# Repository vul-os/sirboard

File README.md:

<h1 align="center">SirBoard</h1>

<p align="center">
  <b>Open hardware for people who would rather prototype than reflow.</b><br>
  107 PCB designs — breakout adapters, development boards and a 39-part sensor line.<br>
  Routed in KiCad. Black soldermask, ENIG gold, 0.1&Prime; pitch.
</p>

## Brand

The mark in [`brand/`](brand/) is the source of truth. Every icon this repo
ships — favicon, PWA and app icons, the mark in the README and on the site — is
rendered from `brand/logo.svg` rather than redrawn, so there is one approved
drawing and no second copy to drift.

Copy it outward, never edit a derived copy, and never edit `brand/` to match
something downstream.

<p align="center">
  <a href="https://vulos.org/projects/sirboard"><b>vulos.org/projects/sirboard</b></a>
  ·
  <a href="docs/OVERVIEW.md">Docs</a>
  ·
  <a href="LICENSE-MIT">MIT OR Apache-2.0</a>
</p>

<p align="center">
  
</p>

---

Most interesting silicon ships in a package that will not sit on a breadboard.
SirBoard answers that in three layers: **bare adapters** you solder the part
onto yourself, **modules** with the part already placed and supported, and
**development boards** with a microcontroller, regulator, USB and headers.

## What's here

| Directory | Contents |
|---|---|
| [`Boards/Breakout/`](Boards/Breakout) | **21 adapters** — QFN, TQFP, SOIC, SOT, USB, MicroSD, coin cells, ESP module carriers |
| [`Boards/Microcontrollers/`](Boards/Microcontrollers) | ATTiny, ATMega328PB/32U4/1284P, ESP32/ESP8266 and SIMCom GNSS carriers |
| [`Boards/Interface/`](Boards/Interface) | USB-to-UART bridges, level shifters, port expanders, a USBASP programmer |
| [`Boards/Sensors/`](Boards/Sensors) | **SirBlue** — 39 digital sensors on one 4-pin JST-SH connector, plus two earlier collections (DigitalSensors 12, AnalogueSensors 2) |
| [`Boards/Modules/`](Boards/Modules) | EEPROM, FRAM, real-time clocks — 5 designs |
| [`Fritzing/`](Fritzing) | 60 hand-drawn breadboard SVGs |

## Quick start

```bash
git clone git@github.com:vul-os/sirboard.git
cd sirboard

# most designs ship a plotted PDF and renders — no tools needed to read one
open Boards/Microcontrollers/SirTiny/ATTinyX16/ATTinyX16.pdf

# or open the project itself
kicad Boards/Microcontrollers/SirTiny/ATTinyX16/ATTinyX16.pro
```

These are **KiCad 5** files (board format `20171130`). KiCad 6 through 9 open
them and offer to convert on save.

## What state is this in?

Hardware repositories rot by ambiguity, so here it is plainly.

**Can you get these made? Yes.** Every one of the 107 designs is fully routed
2-layer copper with a board outline, and plots to gerbers from source with
`kicad-cli` or File → Plot. Nothing here needs a blind via, a buried via,
controlled impedance or a non-standard stack-up, and every outline fits inside a
100 × 100 mm panel. Seven of the fine-pitch breakouts need a 5 mil process
rather than 6 mil — they are named in
[Manufacturing](docs/MANUFACTURING.md#the-5-mil-figure-is-not-decoration--quote-it-to-the-fab).

**What is *not* claimed.** No DRC or ERC report is committed for any board, and
no fabrication or bring-up log exists in this repository. The `_Front`/`_Back`/
`_Iso` images are KiCad 3D-viewer renders, not photographs of assembled boards —
so do not read them as proof that a given design was built and worked. Treat
every design as prototype-grade: **run DRC yourself and read the schematic
before you spend money on a panel.** The catalogue has shipped at least one
unconnected trace in the past (commit `28e6714`, on the TQFP48 breakout), which
is exactly the class of defect a DRC run catches and a render does not.

**Is it maintained?** The designs are stable rather than actively developed. Two
directories under `Boards/` hold a README and no design —
[`Sensors/SirRed`](Boards/Sensors/SirRed) (an analogue line on a 3-pin JST-SH)
and [`Modules/SirReference`](Boards/Modules/SirReference) (voltage references) —
and they are stated intent, not work in progress; neither is counted in the 107.
What *is* maintained is the repository's honesty:
[CI](.github/workflows/ci.yml) gates the counts, coverage tables and fab
figures in these docs against the actual `.kicad_pcb` files on every push, so a
claim here cannot quietly drift away from the copper. Fixes to existing designs
are the most welcome kind of change.

## The sensor line

Every [SirBlue](Boards/Sensors/SirBlue) board carries the same 4-pin 1.00 mm JST-SH
connector — `GND · VCC · SDA · SCL` — and the same outline. One cable fits all
39 parts, so swapping an accelerometer for a time-of-flight ranger is a
connector move rather than a rewire. A
[TCA9548A](Boards/Interface/SirExpand/TCA9548A) multiplexer handles the address
collisions when you want eight of the same part.

## We don't ship driver libraries

Every part here is a standard part with a maintained driver already in the
wild, and [`docs/LIBRARIES.md`](docs/LIBRARIES.md) names the one to install for
each — Adafruit, Pololu, SparkFun, MCUdude's cores, TinyGSM, RTClib.

SirBoard used to fork them. Those forks accumulated no functional changes and
drifted up to 384 commits behind upstream, so they were retired. A stale
driver shipped under our name is worse than no driver at all.

## Documentation

| | |
|---|---|
| [Overview](docs/OVERVIEW.md) | What SirBoard is and how the repository is laid out |
| [Getting started](docs/GETTING-STARTED.md) | Open a design, wire a sensor, install a driver |
| [Breakout adapters](docs/BREAKOUTS.md) | The 21 footprints, and how to pick one |
| [Development boards](docs/BOARDS.md) | Nine families, with the core to install for each |
| [Sensors](docs/SENSORS.md) | The full SirBlue line |
| [Modules](docs/MODULES.md) | Storage, timekeeping, reference |
| [Fritzing parts](docs/FRITZING.md) | The breadboard artwork |
| [Driver libraries](docs/LIBRARIES.md) | Part → upstream library, verified |
| [Manufacturing](docs/MANUFACTURING.md) | Stack-up, gerber export, assembly notes |

## One repository

Every product line lives in this repository, with its full history intact —
`git log -- Boards/Microcontrollers/SirTiny` returns SirTiny's own commits, and
`git blame` still names whoever drew the trace.

## Contributing

Fixes to existing designs are the most welcome kind of change — see
[CONTRIBUTING.md](CONTRIBUTING.md). Commit the KiCad sources and the renders,
never the backups or `fp-info-cache`.

## Licence

[MIT](LICENSE-MIT) OR [Apache-2.0](LICENSE-APACHE) — © VulOS. Fabricate these
designs, modify them, sell the boards. SirBoard is a Vulos project; source and
issues at [github.com/vul-os/sirboard](https://github.com/vul-os/sirboard).

---

<p align="center">
  <sub>Part of <a href="https://vulos.org">Vulos</a> — open by design.</sub>
</p>

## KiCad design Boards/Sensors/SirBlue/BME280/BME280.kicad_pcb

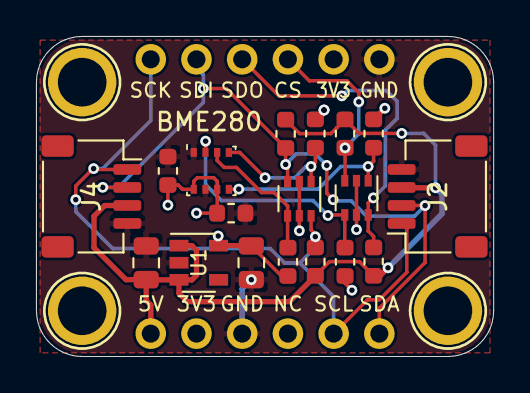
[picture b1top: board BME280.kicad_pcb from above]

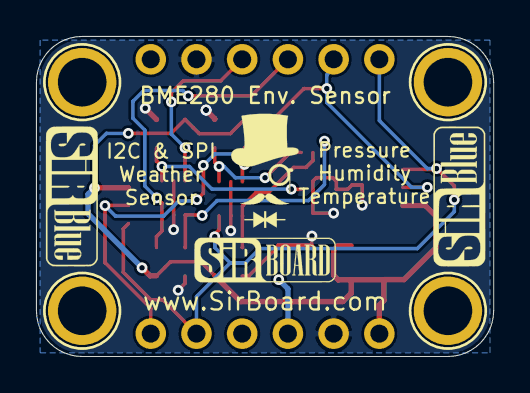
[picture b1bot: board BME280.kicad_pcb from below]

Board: 2 copper layers, 25.4 x 17.8 mm, 24 parts (2 on the bottom side), 11 nets.

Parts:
C1, C4: 10uF; C_0805_2012Metric
C2, C3: 100nF; C_0603_1608Metric
H1, H2, H3, H4: MountingHole; MountingHole_M2.5_SirBoard
J1, J3: Conn_01x06; PinHeader_1x06_P2.54mm_Vertical
J2, J4: Conn_01x04; JST_SH_SM04B-SRSS-TB_1x04-1MP_P1.00mm_Horizontal
Q1, Q2: BSS138DW; SOT-363_SC-70-6
R1, R2, R3, R4, R5, R6, R7, R8: 10K; R_0603_1608Metric
U1: AP2127K-3.3; SOT-23-5
U2: BME280; Bosch_LGA-8_2.5x2.5mm_P0.65mm_ClockwisePinNumbering

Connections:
3V3: C2.1, C3.1, C4.1, J1.2, J3.5, Q1.2, Q1.5, Q2.2, Q2.5, R1.2, R3.2, R5.2, R7.2, U1.5, U2.6, U2.8
5V: C1.1, J1.1, J2.3, J4.3, R2.1, R4.1, R6.1, R8.1, U1.1, U1.3
CS_3V3: Q1.4, R3.1, U2.2
CS_5V: J3.4, Q1.3, R4.2
GND: C1.2, C2.2, C3.2, C4.2, J1.3, J2.4, J3.6, J4.4, U1.2, U2.1, U2.7
SCL_3V3: Q2.1, R5.1, U2.4
SCL_5V: J1.5, J2.1, J3.1, J4.1, Q2.6, R6.2
SDA_3V3: Q2.4, R7.1, U2.3
SDA_5V: J1.6, J2.2, J3.2, J4.2, Q2.3, R8.2
SDO_3V3: Q1.1, R1.1, U2.5
SDO_5V: J3.3, Q1.6, R2.2

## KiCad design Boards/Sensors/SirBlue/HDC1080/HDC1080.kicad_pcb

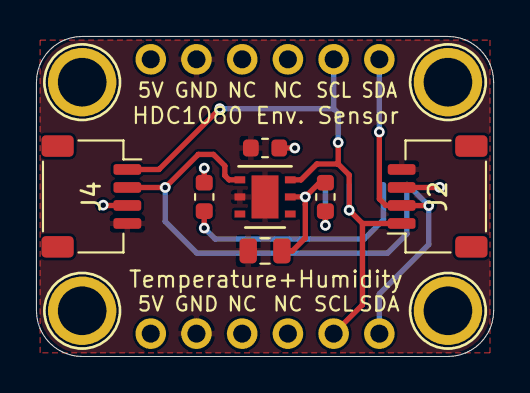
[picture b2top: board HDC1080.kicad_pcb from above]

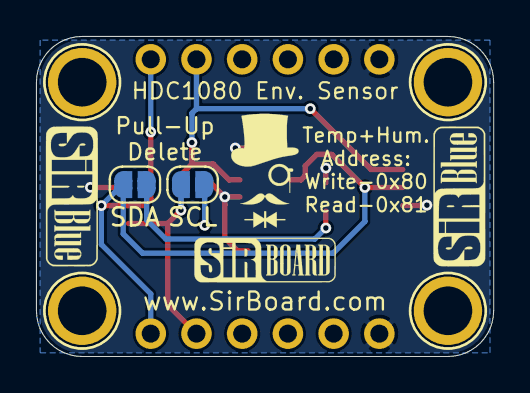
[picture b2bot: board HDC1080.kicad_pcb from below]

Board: 2 copper layers, 25.4 x 17.8 mm, 15 parts (4 on the bottom side), 6 nets.

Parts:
C1: 4.7uF; C_0805_2012Metric
C2: 100nF; C_0603_1608Metric
H1, H2, H3, H4: MountingHole; MountingHole_M2.5_SirBoard
J1, J3: Conn_01x06; PinHeader_1x06_P2.54mm_Vertical
J2, J4: Conn_01x04; JST_SH_SM04B-SRSS-TB_1x04-1MP_P1.00mm_Horizontal
R6, R8: 10K; R_0603_1608Metric
SCL: SolderJumper_2_Open; SolderJumper-2_P1.3mm_Open_RoundedPad1.0x1.5mm
SDA: SolderJumper_2_Open; SolderJumper-2_P1.3mm_Open_RoundedPad1.0x1.5mm
U1: HDC1080; Texas_PWSON-N6

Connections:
5V: C1.1, C2.1, J1.1, J2.3, J3.1, J4.3, R6.1, R8.1, U1.5
GND: C1.2, C2.2, J1.2, J2.4, J3.2, J4.4, U1.2, U1.7
unnamed: R6.2, SCL.1
unnamed: R8.2, SDA.1
SCL: J1.5, J2.1, J3.5, J4.1, SCL.2, U1.6
SDA: J1.6, J2.2, J3.6, J4.2, SDA.2, U1.1

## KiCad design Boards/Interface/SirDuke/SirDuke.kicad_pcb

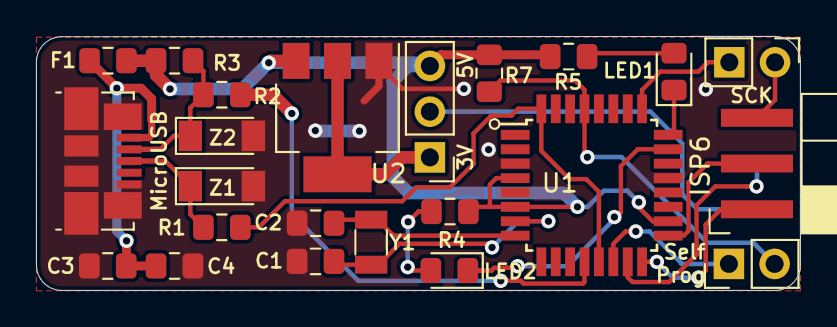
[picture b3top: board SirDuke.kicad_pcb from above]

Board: 2 copper layers, 42.4 x 14.1 mm, 23 parts (0 on the bottom side), 22 nets.

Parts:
3V      5V: Conn_01x03; PinHeader_1x03_P2.54mm_Vertical
C1, C2: 18pF; C_0805_2012Metric_Pad1.15x1.40mm_HandSolder
C3: 100nF; C_0805_2012Metric_Pad1.15x1.40mm_HandSolder
C4: 4u7; C_0805_2012Metric_Pad1.15x1.40mm_HandSolder
F1: 500mA; R_0805_2012Metric_Pad1.15x1.40mm_HandSolder
ISP6: Conn_02x03_Odd_Even; PinSocket_2x03_P2.54mm_Horizontal_SMD
LED1: G; LED_0805_2012Metric_Pad1.15x1.40mm_HandSolder
LED2: R; LED_0805_2012Metric_Pad1.15x1.40mm_HandSolder
MicroUSB: USB_B_Micro; USB_Micro-B_Molex_47346-0001
R1, R2: 68e; R_0805_2012Metric_Pad1.15x1.40mm_HandSolder
R3: 2k2; R_0805_2012Metric_Pad1.15x1.40mm_HandSolder
R4, R5: 1k; R_0805_2012Metric_Pad1.15x1.40mm_HandSolder
R7: 10k; R_0805_2012Metric_Pad1.15x1.40mm_HandSolder
SCK: Conn_01x02; PinHeader_1x02_P2.54mm_Vertical
SelfProg: Conn_01x02; PinHeader_1x02_P2.54mm_Vertical
U1: ATmega8-16AU; TQFP-32_7x7mm_P0.8mm
U2: AMS1117-3.3; SOT-223-3_TabPin2
Y1: Crystal; Crystal_SMD_3215-2Pin_3.2x1.5mm
Z1, Z2: 3.6V; D_MiniMELF

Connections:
unnamed: C1.1, C2.2, C3.2, C4.2, ISP6.6, MicroUSB.5, MicroUSB.6, U1.3, U1.5, U1.21, U2.1, Z1.2, Z2.2
unnamed: C1.2, U1.7, Y1.1
unnamed: C2.1, U1.8, Y1.2
unnamed: C3.1, C4.1, F1.2, MicroUSB.1
unnamed: 3V 5V.3, F1.1, R3.1, R4.1, R5.1, R7.2, U1.4, U1.6, U1.18, U2.3
unnamed: 3V 5V.1, U2.2
unnamed: 3V 5V.2, ISP6.2
unnamed: ISP6.5, SCK.1
unnamed: SCK.2, U1.25
unnamed: SelfProg.1, U1.14
unnamed: R7.1, SelfProg.2, U1.29
unnamed: MicroUSB.2, R2.2, R3.2, Z2.1
unnamed: MicroUSB.3, R1.2, Z1.1
unnamed: ISP6.1, U1.16
unnamed: ISP6.3, U1.17
unnamed: ISP6.4, U1.15
unnamed: LED1.1, U1.24
unnamed: LED1.2, R5.2
unnamed: LED2.1, U1.23
unnamed: LED2.2, R4.2
unnamed: R1.1, U1.13, U1.32
unnamed: R2.1, U1.12

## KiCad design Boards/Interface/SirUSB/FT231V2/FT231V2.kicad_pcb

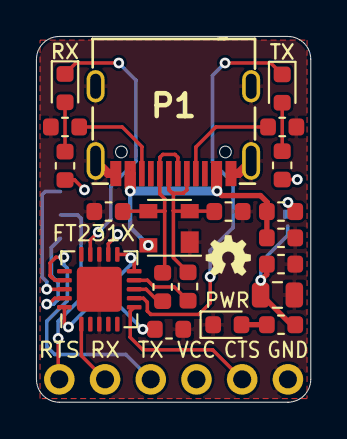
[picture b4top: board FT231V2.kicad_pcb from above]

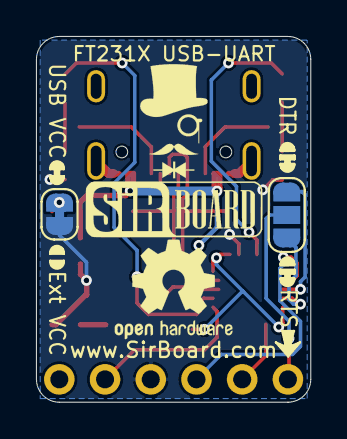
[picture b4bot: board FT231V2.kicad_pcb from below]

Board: 2 copper layers, 15.2 x 20.3 mm, 23 parts (2 on the bottom side), 22 nets.

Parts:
C1: 10nF; C_0603_1608Metric
C2, C3: 47pF; C_0603_1608Metric
C4, C6: 100nF; C_0603_1608Metric
C5: 4.7uF; C_0805_2012Metric
D1: PRTR5V0U2X; SOT-143
FB1: 40E@100MHz; L_0603_1608Metric
J1: Conn_01x06; PinHeader_1x06_P2.54mm_Horizontal
JP1: SolderJumper_2_Open; SolderJumper-2_P1.3mm_Bridged_RoundedPad1.0x1.5mm
P1: USB_C_Plug_USB2.0; USB_C
P6: SolderJumper_3_Open; SolderJumper-3_P1.3mm_Open_RoundedPad1.0x1.5mm
PWR: RED; LED_0603_1608Metric
R1, R2: 27e; R_0603_1608Metric
R3, R4, R5: 1k; R_0603_1608Metric
R6, R7: 5k1; R_0603_1608Metric
RX: GREEN; LED_0603_1608Metric
TX: GREEN; LED_0603_1608Metric
U1: FT231XQ; QFN-20-1EP_4x4mm_P0.5mm_EP2.5x2.5mm

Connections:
CBUS1: RX.1, U1.14
CBUS2: TX.1, U1.7
CTS: J1.2, U1.6
D+: C2.1, D1.3, P1.A6, P1.B6, R2.2
D-: C3.1, D1.2, P1.A7, P1.B7, R1.1
DTR: P6.3, U1.18
GND: C1.2, C2.2, C3.2, C4.2, C5.2, C6.2, D1.1, J1.1, P1.A1, P1.A12, P1.B1, P1.B12, P1.S1, PWR.1, R6.2, R7.2, U1.3, U1.13, U1.21
unnamed: C6.1, U1.10, U1.11, U1.20
unnamed: FB1.1, JP1.1
unnamed: P1.A5, R7.1
unnamed: P1.B5, R6.1
unnamed: PWR.2, R4.2
unnamed: R3.2, TX.2
unnamed: R5.2, RX.2
P6: J1.6, P6.2
RTS: P6.1, U1.19
RX: J1.5, U1.1
TX: J1.4, U1.17
VCC: C4.1, C5.1, J1.3, JP1.2, R3.1, R4.1, R5.1, U1.12
VUSB: C1.1, D1.4, FB1.2, P1.A4, P1.A9, P1.B4, P1.B9
uD+: R2.1, U1.8
uD-: R1.2, U1.9

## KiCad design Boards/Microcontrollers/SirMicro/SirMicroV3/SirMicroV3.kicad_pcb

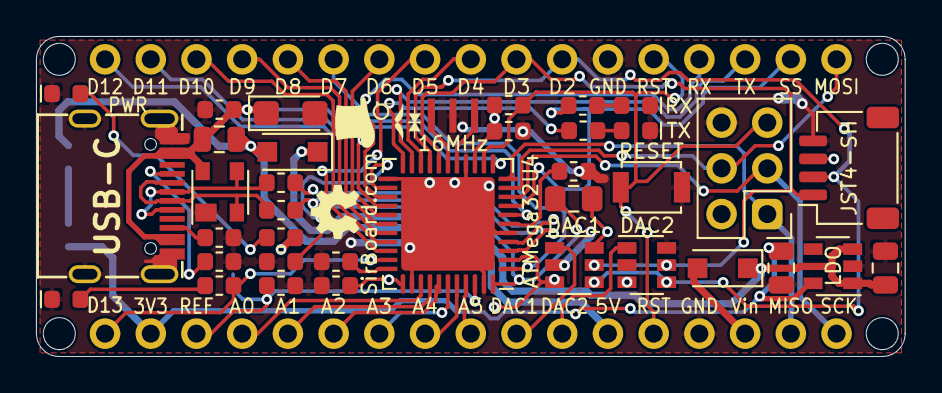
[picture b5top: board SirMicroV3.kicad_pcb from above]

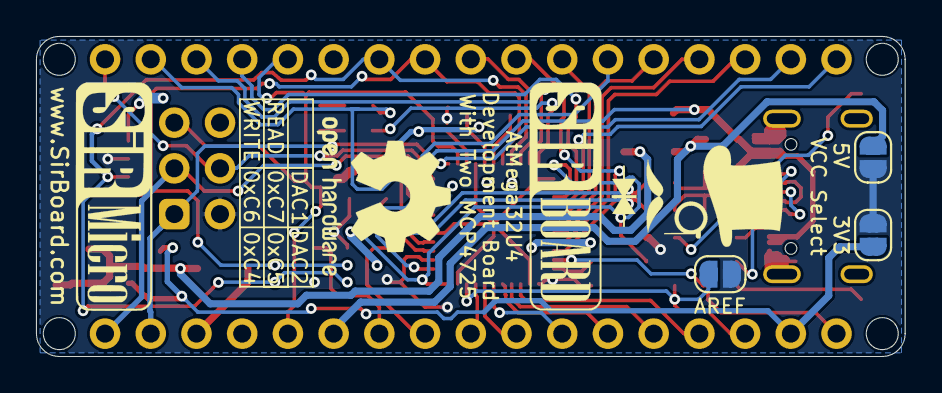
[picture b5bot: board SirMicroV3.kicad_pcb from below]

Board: 2 copper layers, 48.3 x 17.8 mm, 46 parts (5 on the bottom side), 51 nets.

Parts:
C1, C3, C4: 100nF; C_0603_1608Metric
C2, C9: 1uF; C_0603_1608Metric
C5, C7: 10uF; C_0805_2012Metric
C6: 10nF; C_0603_1608Metric
C8: 22uF; CP_EIA-3216-12_Kemet-S
D1: PRTR5V0U2X; SOT-143
D2, D3: MBR120; D_SOD-123F
D13: LED; LED_0603_1608Metric
DAC1, DAC2: MCP4725; SOT-23-6
F1: 500mA; R_0805_2012Metric
H1, H2, H3, H4: MountingHole; MountingHole_2.2mm_M2
J1, J2: Conn_01x17; PinHeader_1x17_P2.54mm_Vertical
J4: Conn_02x03_Odd_Even; PinHeader_2x03_P2.54mm_Vertical
JP1: AREF; SolderJumper-2_P1.3mm_Open_RoundedPad1.0x1.5mm
JP2, JP3: SolderJumper_2_Open; SolderJumper-2_P1.3mm_Open_RoundedPad1.0x1.5mm
JST4-SH: SirBlue; SirBlue_Connector
L1: 10uH; L_0805_2012Metric_Pad1.15x1.40mm_HandSolder
LDO: SPX3819M5-L-3-3; SOT-23-5
PWR: LED; LED_0603_1608Metric
R1, R2: 22e; R_0603_1608Metric
R3, R5: 10k; R_0603_1608Metric
R4, R8, R9, R10: 1k; R_0603_1608Metric
R11, R12: 5K1; R_0603_1608Metric
RESET: SW_Push; SW_SPST_B3U-1000P
RX: LED; LED_0603_1608Metric
TX: LED; LED_0603_1608Metric
U1: ATmega32U4-MU; QFN-44-1EP_7x7mm_P0.5mm_EP5.2x5.2mm
USB-C: USB_C_Plug_USB2.0; USB_C
Y1: 20MHz; Resonator_SMD_muRata_CSTxExxV-3Pin_3.0x1.1mm

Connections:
3V3: C7.1, J2.16, JP3.1, LDO.5
/D13LED: D13.2, R9.2
/HWB: R5.2, U1.33
/PWRLED: PWR.2, R10.2
/RXLED: R4.2, RX.2
/TXLED: R8.2, TX.2
/UCAP: C2.1, U1.6
/X1: U1.16, Y1.1
/X2: U1.17, Y1.3
A0: J2.14, U1.36
A1: J2.13, U1.37
A2: J2.12, U1.38
A3: J2.11, U1.39
A4: J2.10, U1.40
A5: J2.9, U1.41
AREF: C1.1, J2.15, JP1.2, U1.42
D4: J1.9, U1.20
D5: J1.10, U1.31
D6: J1.11, U1.27
D7: J1.12, U1.1
D8: J1.13, U1.28
D9: J1.14, U1.29
D10: J1.15, U1.30
D11: J1.16, U1.12
D12: J1.17, U1.26
D13: J2.17, R9.1, U1.32
D+: D1.3, R1.1, USB-C.A6, USB-C.B6
D-: D1.2, R2.1, USB-C.A7, USB-C.B7
GND: C1.2, C2.2, C3.2, C4.2, C5.2, C6.2, C7.2, C8.2, C9.2, D1.1, D13.1, DAC1.2, DAC2.2, DAC2.6, J1.6, J2.4, J4.6, JST4-SH.4, LDO.2, PWR.1, R5.1, R11.1, R12.1, RESET.2, RX.1, TX.1, U1.5, U1.15, U1.23, U1.35, U1.43, U1.45, USB-C.A1, USB-C.A12, USB-C.B1, USB-C.B12, USB-C.S1, Y1.2
MISO: J2.2, J4.1, U1.11
MOSI: J1.1, J4.4, U1.10
unnamed: C5.1, D2.1, D3.1, LDO.1, LDO.3
unnamed: C9.1, L1.2, U1.24, U1.44
unnamed: R12.2, USB-C.A5
unnamed: R11.2, USB-C.B5
RESET: J1.5, J2.5, J4.5, R3.2, RESET.1, U1.13
RX: J1.4, U1.25
RX_LED: J1.2, R4.1, U1.8
SCK: J2.1, J4.3, U1.9
SCL: DAC1.5, DAC2.5, J1.8, JST4-SH.1, U1.18
SDA: DAC1.4, DAC2.4, J1.7, JST4-SH.2, U1.19
TX: J1.3, U1.21
TX_LED: R8.1, U1.22
VBUS: C6.1, C8.1, D1.4, F1.2, U1.7, USB-C.A4, USB-C.A9, USB-C.B4, USB-C.B9
VCC: C3.1, C4.1, DAC1.3, DAC1.6, DAC2.3, J4.2, JP1.1, JP2.2, JP3.2, JST4-SH.3, L1.1, R3.1, R10.1, U1.2, U1.14, U1.34
VIN: D3.2, J2.3
VO1: DAC1.1, J2.8
VO2: DAC2.1, J2.7
VUSB: D2.2, F1.1, J2.6, JP2.1
uD+: R1.2, U1.4
uD-: R2.2, U1.3

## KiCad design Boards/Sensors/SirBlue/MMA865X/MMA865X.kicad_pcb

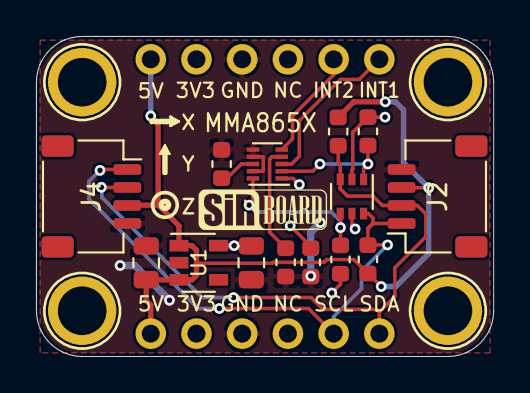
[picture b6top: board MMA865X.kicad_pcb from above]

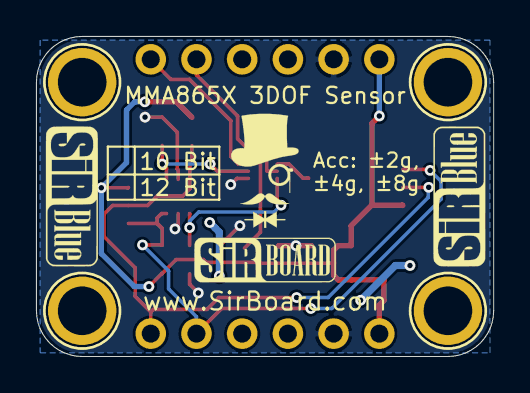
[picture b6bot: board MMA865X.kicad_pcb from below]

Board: 2 copper layers, 25.4 x 17.8 mm, 20 parts (2 on the bottom side), 11 nets.

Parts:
C1, C4: 10uF; C_0805_2012Metric
C2, C5: 100nF; C_0603_1608Metric
C3: 220nF; C_0603_1608Metric
H1, H2, H3, H4: MountingHole; MountingHole_M2.5_SirBoard
J1, J3: Conn_01x06; PinHeader_1x06_P2.54mm_Vertical
J2, J4: Conn_01x04; JST_SH_SM04B-SRSS-TB_1x04-1MP_P1.00mm_Horizontal
Q2: BSS138DW; SOT-363_SC-70-6
R5, R6, R7, R8: 10K; R_0603_1608Metric
U1: AP2127K-3.3; SOT-23-5
U2: MMA865X; DFN-10_2x2mm_P0.4mm

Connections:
3V3: C3.1, C4.1, J1.2, J3.2, Q2.2, Q2.5, R5.2, R7.2, U1.5, U2.1
5V: C1.1, J1.1, J2.3, J3.1, J4.3, R6.1, R8.1, U1.1, U1.3
GND: C1.2, C2.2, C3.2, C4.2, C5.2, J1.3, J2.4, J3.3, J4.4, U1.2, U2.6, U2.7, U2.9
INT1: J3.6, U2.3
INT2: J3.5, U2.5
unnamed: C2.1, U2.4
unnamed: C5.1, U2.8
SCL_3V3: Q2.1, R5.1, U2.2
SCL_5V: J1.5, J2.1, J4.1, Q2.6, R6.2
SDA_3V3: Q2.4, R7.1, U2.10
SDA_5V: J1.6, J2.2, J4.2, Q2.3, R8.2

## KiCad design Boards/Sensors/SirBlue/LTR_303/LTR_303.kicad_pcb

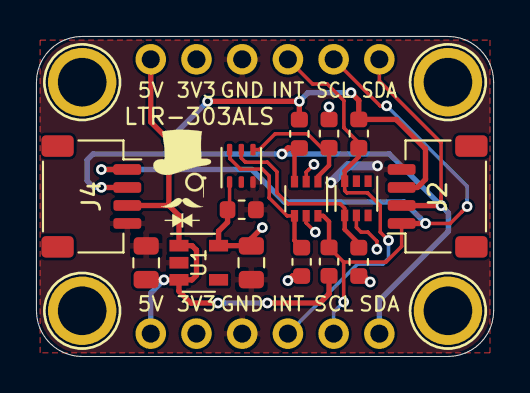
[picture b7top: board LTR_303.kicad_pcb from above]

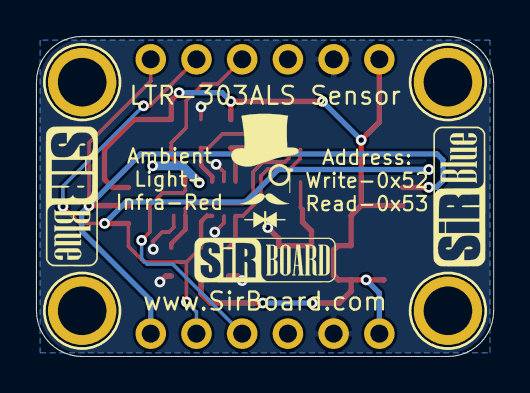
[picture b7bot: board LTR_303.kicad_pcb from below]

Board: 2 copper layers, 25.4 x 17.8 mm, 21 parts (2 on the bottom side), 9 nets.

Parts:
C1, C4: 10uF; C_0805_2012Metric
C2: 100nF; C_0603_1608Metric
H1, H2, H3, H4: MountingHole; MountingHole_M2.5_SirBoard
J1, J3: Conn_01x06; PinHeader_1x06_P2.54mm_Vertical
J2, J4: Conn_01x04; JST_SH_SM04B-SRSS-TB_1x04-1MP_P1.00mm_Horizontal
LTR-303ALS: LTR-303ALS-01; Lite-On_LTR-303ALS-01
Q1, Q2: BSS138DW; SOT-363_SC-70-6
R3, R4, R5, R6, R7, R8: 10K; R_0603_1608Metric
U1: AP2127K-3.3; SOT-23-5

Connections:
3V3: C2.1, C4.1, J1.2, J3.2, LTR-303ALS.1, Q1.5, Q2.2, Q2.5, R3.2, R5.2, R7.2, U1.5
5V: C1.1, J1.1, J2.3, J3.1, J4.3, R4.1, R6.1, R8.1, U1.1, U1.3
GND: C1.2, C2.2, C4.2, J1.3, J2.4, J3.3, J4.4, LTR-303ALS.3, U1.2
INT_3V3: LTR-303ALS.5, Q1.4, R3.1
INT_5V: J1.4, J3.4, Q1.3, R4.2
SCL_3V3: LTR-303ALS.4, Q2.1, R5.1
SCL_5V: J1.5, J2.1, J3.5, J4.1, Q2.6, R6.2
SDA_3V3: LTR-303ALS.6, Q2.4, R7.1
SDA_5V: J1.6, J2.2, J3.6, J4.2, Q2.3, R8.2

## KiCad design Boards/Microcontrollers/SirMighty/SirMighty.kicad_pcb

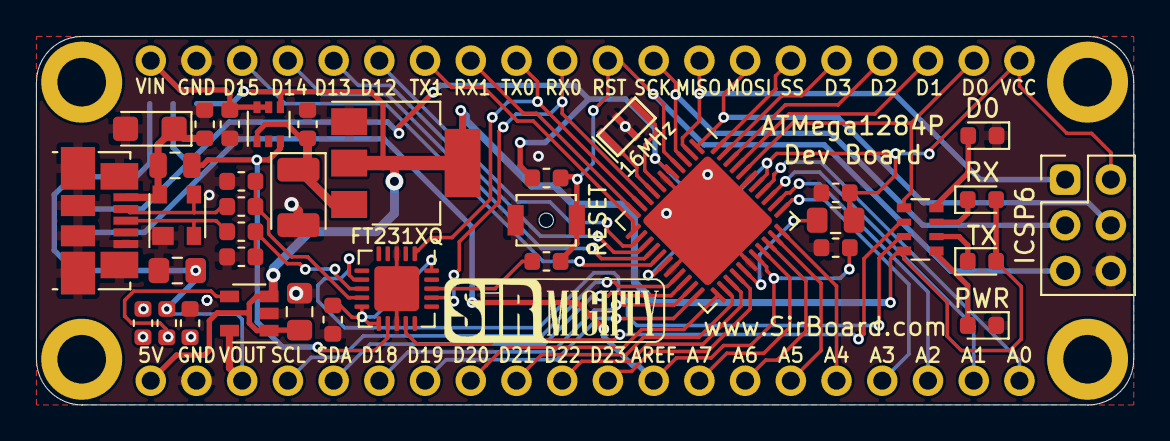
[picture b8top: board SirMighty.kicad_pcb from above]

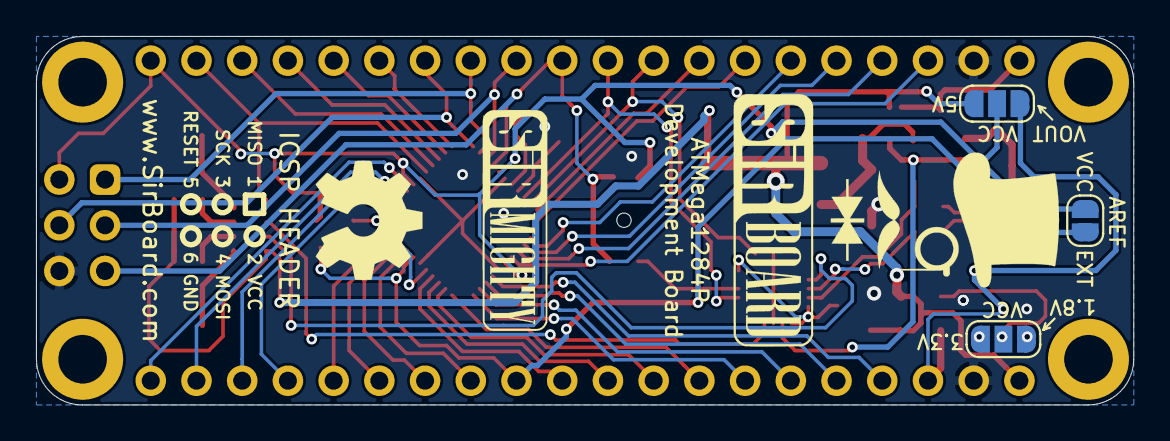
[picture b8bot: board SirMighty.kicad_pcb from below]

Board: 2 copper layers, 61.0 x 20.5 mm, 41 parts (5 on the bottom side), 60 nets.

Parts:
16MHz: 16MHz; Resonator_SMD_muRata_CSTxExxV-3Pin_3.0x1.1mm
C1, C5, C7, C11, C12: 100nF; C_0603_1608Metric
C2, C4: 47pF; C_0603_1608Metric
C3: 22uF; CP_EIA-3528-12_Kemet-T
C6: 10nF; C_0603_1608Metric
C8: 22uF; CP_EIA-3216-12_Kemet-S
C9, C10: 1uF; C_0805_2012Metric_Pad1.15x1.40mm_HandSolder
D0: LED; LED_0603_1608Metric
D1: PRTR5V0U2X; SOT-143
F1: 500mA; R_0805_2012Metric
FT231XQ: FT231XQ; QFN-20-1EP_4x4mm_P0.5mm_EP2.5x2.5mm
ICSP6: Conn_02x03_Odd_Even; PinHeader_2x03_P2.54mm_Vertical
J1, J2: Conn_01x20; PinHeader_1x20_P2.54mm_Vertical
J3: USB_B_Micro; USB_Micro-B_Molex_47346-0001
JP1: SolderJumper_2_Open; SolderJumper-2_P1.3mm_Open_RoundedPad1.0x1.5mm
JP2, JP3: SolderJumper_3_Open; SolderJumper-3_P1.3mm_Open_RoundedPad1.0x1.5mm
L1: 10uH; L_0805_2012Metric_Pad1.15x1.40mm_HandSolder
PWR: LED; LED_0603_1608Metric
Q1: Q_DUAL_PMOS_S1G1D2S2G2D1; SOT-363_SC-70-6
R1, R2: 27e; R_0603_1608Metric
R3, R4: 10k; R_0603_1608Metric
R5: 56k; R_0603_1608Metric
R6: 22k; R_0603_1608Metric
R7: 68k; R_0603_1608Metric
RESET: SW_Push; SW_SPST_B3U-1000P-B
RN1: 1k; R_Array_Convex_4x0603
RX: LED; LED_0603_1608Metric
TX: LED; LED_0603_1608Metric
U2: AP7365-W-7; SOT-23-5
U4: AZ1117-5.0; SOT-223-3_TabPin2
www.SirBoard.com: ATmega1284P-MU; QFN-44-1EP_7x7mm_P0.5mm_EP5.2x5.2mm

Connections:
3.3V: C12.2, FT231XQ.10, FT231XQ.11, FT231XQ.20
5V: C9.1, J1.1, JP3.3, Q1.4, RN1.4, RX.2, TX.2, U2.1, U2.3, U4.2
/D0LED: D0.2, RN1.8
/PWRLED: PWR.2, RN1.5
/X1: 16MHz.3, www.SirBoard.com.8
/X2: 16MHz.1, www.SirBoard.com.7
/uD+: C2.1, FT231XQ.8, R2.2
/uD-: C4.1, FT231XQ.9, R1.2
A0: J1.20, www.SirBoard.com.37
A1: J1.19, www.SirBoard.com.36
A2: J1.18, www.SirBoard.com.35
A3: J1.17, www.SirBoard.com.34
A4: J1.16, www.SirBoard.com.33
A5: J1.15, www.SirBoard.com.32
A6: J1.14, www.SirBoard.com.31
A7: J1.13, www.SirBoard.com.30
ADJ: JP2.2, R7.2, U2.4
AREF: C1.1, J1.12, JP1.1, www.SirBoard.com.29
D0: J2.19, RN1.1, www.SirBoard.com.40
D1: J2.18, www.SirBoard.com.41
D2: J2.17, www.SirBoard.com.42
D3: J2.16, www.SirBoard.com.43
D12: J2.6, www.SirBoard.com.13
D13: J2.5, www.SirBoard.com.14
D14: J2.4, www.SirBoard.com.15
D15: J2.3, www.SirBoard.com.16
D18: J1.6, www.SirBoard.com.21
D19: J1.7, www.SirBoard.com.22
D20: J1.8, www.SirBoard.com.23
D21: J1.9, www.SirBoard.com.24
D22: J1.10, www.SirBoard.com.25
D23: J1.11, www.SirBoard.com.26
D+: D1.2, J3.3, R2.1
D-: D1.3, J3.2, R1.1
GND: 16MHz.2, C1.2, C2.2, C3.2, C4.2, C5.2, C6.2, C7.2, C8.2, C9.2, C10.2, C12.1, D0.1, D1.1, FT231XQ.3, FT231XQ.13, FT231XQ.21, ICSP6.6, J1.2, J2.2, J3.5, J3.6, PWR.1, R4.2, R5.2, R6.2, RESET.2, U2.2, U4.1, www.SirBoard.com.6, www.SirBoard.com.18, www.SirBoard.com.28, www.SirBoard.com.39, www.SirBoard.com.45
MISO: ICSP6.1, J2.13, www.SirBoard.com.2
MOSI: ICSP6.4, J2.14, www.SirBoard.com.1
unnamed: C3.1, C5.1, Q1.1, U4.3
unnamed: C11.2, FT231XQ.18
unnamed: JP2.1, R6.1
unnamed: JP2.3, R5.1
unnamed: L1.2, www.SirBoard.com.27
unnamed: RN1.6, TX.1
unnamed: RN1.7, RX.1
RESET: C11.1, ICSP6.5, J2.11, R3.2, RESET.1, www.SirBoard.com.4
RXD0: FT231XQ.17, J2.10, www.SirBoard.com.9
RXD1: J2.8, www.SirBoard.com.11
RX_LED: FT231XQ.14, RN1.2
SCK: ICSP6.3, J2.12, www.SirBoard.com.3
SCL: J1.4, www.SirBoard.com.19
SDA: J1.5, www.SirBoard.com.20
SS: J2.15, www.SirBoard.com.44
TXD0: FT231XQ.1, J2.9, www.SirBoard.com.10
TXD1: J2.7, www.SirBoard.com.12
TX_LED: FT231XQ.7, RN1.3
VCC: C7.1, ICSP6.2, J2.20, JP1.2, JP3.2, L1.1, R3.1, www.SirBoard.com.5, www.SirBoard.com.17, www.SirBoard.com.38
VIN: J2.1, Q1.5, Q1.6, R4.1
VOUT: C10.1, J1.3, JP3.1, R7.1, U2.5
VUSB: F1.1, FT231XQ.12, Q1.2, Q1.3
Vbus: C6.1, C8.1, D1.4, F1.2, J3.1

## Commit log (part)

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2019-07-04 Initial Board
2019-07-10 SOIC20 and SOIC28 Added
2019-07-11 QFN20 & QFN16 Added
2019-07-16 USB to UART Modules
2019-07-16 remove submodule
2019-07-16 fixed git issue
    fuck windows
2019-07-16 4 Channel Bi-Directional Level Shifter
2019-07-17 8 Channel Bi-Directional Level Shifter
2019-07-20 Initial Commit of 5V variant
2019-07-20 PCB Silkscreen revised
2019-07-20 Board Layout revised and 3V3 Version Added
2019-07-20 Jumper Edited
2019-07-21 ATTiny85 Added
2019-07-22 ATTiny "1 Series" AVR Development boards added
2019-07-23 SOIC24 Added
2019-07-24 TQFP/QFN48 Added
2019-07-24 Attiny3217 Updated
2019-07-25 Silkscreens and sizes updated
2019-07-25 Silkscreens Updated
2019-07-26 SOIC8 Changed to TSSOP8
2019-07-26 Silkscreen Updates
2019-07-26 Silkscreens Updated and Board Outlines aligned
2019-07-27 Dual Voltage And Voltage Selector Added, QFN Package used
2019-07-28 QFN16 Revised
2019-07-28 Jumpers Moved
2019-07-28 Final Revisions
2019-07-31 Dimension Edits
2019-07-31 QFN16 Copper Pour Revised
2019-07-31 Dimensions Added And TQFP64 Added
2019-08-04 Pin Numbering edited
2019-08-06 Spacings Updated
2019-08-06 Dimensions Updated
2019-08-20 Layout updated and silkscreen revised
2019-08-20 New Multi-Voltage Layout
2019-08-20 Silkscreens Orientated
2019-08-20 Power LED Added
2019-08-21 LDO changed
2019-08-21 LDO capacitors edited
2019-08-21 Fuse Footprint changed
2019-09-09 Final Revision
2019-09-09 Regulator changed from AP to AZ
2019-09-09 Power LED edited
2019-09-09 Silkscreen Updated
2019-09-19 Silkscreen Edits
    Dimensions moved to Drawings Layer
2019-09-19 Capacitor Footprint change
    3216 to 3512
2019-09-19 Capacitor Footprint changed
    3216 to 3512
2019-10-26 initialise project
2019-10-26 add sch for TCA9548A
2019-10-29 USB, SD and CR Cells Added
    MicroSD, MicroUSB, MiniUSB, USB-C, CR1220, CR2032 added as well as all schematics page sizes optimised
2019-10-29 SIM28 Initial commit
2019-11-06 Layout Updated
2019-11-06 SIM39EAU Initial Commit
2019-11-06 SIM68M Initial Commit
2019-11-06 BMP280, BME280, BME680 Initial Commit
    Environmental Sensors
2019-12-02 MCP9808 Added
    Initial Commit
2019-12-02 Page Settings Updated
2019-12-02 GNSS Boards Page Layout Updates
2019-12-02 TCA9548A Added
    Initial Commit
2019-12-02 DS1307ZN+ RTC
    Initial Commit
2019-12-04 Part Numbers Added
2019-12-04 Part Numbers Added
    Minor board Revisions
2019-12-06 SirKeep initial Commmit
    FRAM and EEPROM Modules added
2019-12-10 LED Update
2019-12-10 SIM868 Initial Commit
2019-12-17 added ADLX337 firmware example
2019-12-18 add micropython code
2019-12-21 ADS1X15 Added in place of ADS1015 and ADS1115
2019-12-21 ADXL32X Initial Commit
    ADXL325, ADXL326 and ADXL327 Breakout
2019-12-21 Library Edit
2019-12-21 24LCXXX Added in place of 24512
2019-12-21 MB85RXXX Added in place of MB85RC256V
2019-12-21 MB85RSXXX Added in place of MB85RS256
2019-12-21 ADXL345 Initial Commit
2019-12-21 LSM303 Initial Commit
2019-12-21 MCP4725 InitialCommit
2019-12-21 MMA845X Initial Commit
2019-12-21 BME280 Part number edits
2019-12-21 PCA9534 Initial Commit
2019-12-21 DS3231M Initial Commit
2019-12-21 DS1307ZN+ Board form factor update
    Unified with DS3231
2019-12-21 SirMicro5V and SirMicro3V3 Removed
2019-12-21 SirNano5V, SirNano3V3, SirNano1V8 removed
2019-12-21 MicroSDv2 Removed and MicroSD and MicroSD_DualVoltage Updated
2019-12-31 FXOS8700 Initial Commit
    Digital 14Bit bit Accelerometer and 16 Bit Magnetometer with I2C and SPI
2020-01-08 Schematic PDF and 3D Renders added
2020-01-08 MCP4728 Initial Commit
    4 Channel I2C DAC
2020-01-09 Part numbers added for all variants
2020-01-09 Part number added
2020-01-09 CCS811 initial commit
2020-01-10 LSM6DS33 Initial Commit
    Accelerometer/Gyrometer
2020-01-17 Minor Layout Updates
2020-01-17 CH330N Initial Commit
2020-01-17 CH340E Initial Commit
2020-01-17 CH340G Revision 2
2020-01-21 SirBlue - ADXL345 Initial Commit
    I2C+SPI Accelerometer
2020-01-21 SirBlue - BME280 Initial Commit
    Temperature, Pressure and Humidity Sensor
2020-01-21 SirBlue - BMP280 Initial Commit
    Temperature and Pressure Sensor
2020-01-21 SirBlue - CCS811 Initial Commit
    eCO2 and VOC Sensor
2020-01-21 SirBlue - FXOS8700 Initial Commit
    6DOF - Accelerometer and Magnetometer Sensor
2020-01-21 SirBlue - L3G4200 Initial Commit
    I2C+SPI Gyroscope
2020-01-21 SirBlue - LSM303 Initial Commit
    6DOF - Accelerometer and Magnetometer Sensor
2020-01-21 SirBlue - LSM6DS33 Initial Commit
    6DOF - Accelerometer and Gyroscope Sensor
2020-01-23 SirBlue - MMA845X Initial Commit
    Dual Chip Breakout for 3DOF Accelerometers MMA8451 and MMA8452
2020-01-24 SirBlue - MCP4728 Initial Commit
    4 Channel I2C DAC
2020-01-24 SirBlue - MCP9808 initial Commit
    High Accuracy I2C Temperature Sensor
2020-01-28 MMA845X PCB and SCH edit
    Extra Power Pins Added
2020-01-28 Copper Pour Edits
    Copper pour reduced to have 0.2mm edge clearance
2020-01-30 Ground Plane edit
    Joint Added
2020-01-30 ADS1X15 Initial Commit
    Dual Breakout for the ADS1015 and ADS1115 4 Channel ADC with 12 or 16 Bit Output
2020-01-30 LTR-303ALS Initial Commit
    Ambient Light Sensor Breakout
2020-01-30 LTR-381RGB Initial Commit
    Ambient Light, Colour and InfraRed Sensor
2020-01-30 SHT3XD Initial Commit
    Dual Breakout for the SHT30D and SHT31D Temperature and Humidity Sensors
2020-02-07 Board Redesign
    Revision3
2020-02-07 Board size updated
    Board size changed from 33.02mmX26.035mm to 33.02mmX25.4mm
2020-02-08 Board Redesign
2020-02-08 Board Sizes Updated
2020-02-08 Board Sizes Reduced in Width by 0.254mm
2020-02-08 FTDI Boards With USB-C Initial Commit
2020-02-08 Board Size Updated
2020-02-09 MCP4725 Initial Commit
    1 Channel I2C DAC with 12 Bits resolution
2020-02-09 TCA9548 Initial Commit
    I2C Multiplexer with 1mm JST SH Connectors
2020-02-09 MCP9808 .sch and .pcb update
    Address Pins Broken Out
2020-02-09 SirBlue - DS1307Z Initial Commit
2020-02-09 SirBlue - DS3231M Initial Commit
2020-03-05 SirMicro Version 3 Added
    USB-C, Dual MCP4725 DACs, SirBlue (Qwiic, Stemma QT) Connector, Arduino Micro Form Factor + Pinout
2020-03-05 SirNano Renamed SirNanoV2
2020-03-05 SirNanoV3 Added
    MicroUSB changed to USB-C, LDO changed from AP7365 to SPX3819, SirBlue (Qwiic, Stemma QT, etc) Connector, ICSP Header Removed
2020-03-06 LIS3MDL Initial Commit
    3-Axis Magnetometer from STM broken out onto the SirBlue form factor
2020-03-06 MMA865X Initial Commit
    3-Axis Accelerometers broken out onto the SirBlue Form Factor. MMA8652 and MMA8653 compatible
2020-03-06 SirBlue - TCA9534 Initial Commit
    I2C Bus Port expander broken out onto the SirBlue form factor
2020-03-06 SirBlue - MB85RCXXX Initial Commit
    FRAM memory broken out onto the SirBlue form factor
2020-03-07 Schematic.pdf added
2020-03-07 LISDH12 Initial Commit
    Digital I2C and SPI "femto" 3-Axis Accelerometer
2020-03-07 Schematic.pdf added for LIS2DH12
2020-03-10 Silkscreen Edit
    VOC and Temperature swopped around
2020-03-10 Board Revision
    Ground plane joined, SCL, SDA and INT broken out on both sides of headers
2020-03-10 Board Revision
    SDA and SCL were not connected from the jumpers to the Headers. Fixed
2020-03-10 BMA255 Initial Commit
    Bosch Sensortech 3 DOF Accelerometer Broken out onto the SirBlue Form Factor
2020-03-10 BMI055 Initial Commit
    Bosch Sensortech 6 DOF Accelerometer and Gyroscope Broken out onto the SirBlue Form Factor - Hardware for I2C only
2020-03-10 BMI160
    Bosch Sensortech 6 DOF Accelerometer and Gyroscope Broken out onto the SirBlue Form Factor with I2C and SPI
2020-03-10 .pdf Updated
2020-03-10 BMX055 Initial Commit
    Bosch Sensortech 9 DOF Accelerometer, Gyroscope and Magnetometer Broken out onto the SirBlue Form Factor - Hardware for I2C only
2020-03-10 Auto stash before revert of "Board Revision"
2020-03-10 Revert "Auto stash before revert of "Board Revision""
    This reverts commit b52b09b8dd794bd49e9659377365344e763f0be5.
2020-03-10 Phew...
    almost a screw up
2020-03-11 BMX055 - .pcb Updated
2020-03-11 BNO055 Initial Commit
    Absolute Orientation 9DOF Sensor on the SirBlue form Factor
2020-03-11 ADXL345 Silkscreen edit
    ADXL345 Added to front silkscreen
2020-03-11 ADXL375 Initial Commit
    ±200g I2C and SPI Accelerometer
2020-03-11 MMA845X Update
    MMA8453 Added - 10 Bit Version
2020-03-12 Soldermask width adjusted
2020-03-12 Board Updates
2020-03-12 BME680 3D render changed
2020-03-12 VL53L0X Initial Commit
    2m time of Flight Sensor
2020-03-12 VL53L1X Initial Commit
    4m time of Flight Sensor
2020-03-12 SirUSB Updates
    3D Renders changed to white solder mask. CH330N TX and RX references moved
2020-03-12 Minor Updates
2020-03-19 ADXL375 Schematic Update
    ADXL345 changed to ADXL375
2020-03-19 BME/P280 3D render changed
    .jpeg files and 3D file changed
2020-03-19 Schematic and 3D render updates
    Multiple boards
2020-03-19 HDC1080 Initial Commit
    TI Temperature and Humidity Sensor
2020-03-19 APDS-9960 Initial commit
    Digital Ambient, Colour, Proximity and Gesture control Optical Module
2020-03-19 HTS211 Initial Commit
    STM Humidity and Temperature Sensor
2020-03-19 LPS22HB Initial Commit
    STM Pressure and Temperature Sensor
2020-03-19 Schematic Update - SirMicroR3
    20Mhz Changed to 16Mhz
2020-03-19 SirNanoR3 Update
    20MHz Murata 3115 Resonator changed to 20MHz 3225_4P Resonator
2020-03-19 HTS221 Schema update
2020-03-19 SirMicroR3 Update
    Silkscreen Edits
2020-04-07 CH340G Fix
    5k1 Resistors added to CC1 and CC2, TX and RX LEDs pulled up to VCC,Copper Pour changed from 3V3 to VCC.
2020-04-07 CH340E Fix
    5k1 Resistors added to CC1 and CC2, TX and RX LEDs pulled up to VCC,Copper Pour changed from 3V3 to VCC.
2020-04-11 SiRUSB Updates
    USB-C 3D Renders Added and Pictures Updated
2020-04-11 Revision3.1
    Layout Improved, PE0 and PE1 used for SirBlue Connector + USB-C 3D Renders Added and Pictures Updated
2020-04-11 SirMicro Update
    USB-C 3D Renders Added and Pictures Updated
2020-04-12 SirUSB Updates
    CH330N Revision 1.1 + 3D Render Improvement
2020-04-12 CH3XX Boards Schematics Updated
    .pdf update
2020-04-12 CP2104 Initial Commit
    Silicon Labs USB-UART Converter
2020-04-19 Breakout Boards Revision 2
    Renders updated, silkscreen text improved, blurry silkscreen items removed/resized.
2020-04-20 ESP-12F Initial Commit
    ESP-12F Module Breakout
2020-04-20 ESP-WROOM-02 Initial Commit
    ESP-WROOM-02 Breakout
2020-04-20 SirNano Silkscreen Widened
2020-04-21 ESP-12F Update
    Module moved higher to allow antenna to be placed off the board.
2020-04-21 CP2102N_QFN20 Initial Commit
2020-04-21 SirUSB Board Revisions
    Removed MicroUSB Versions of FT230 and FT231, SolderPaste Layer Adjusted to -0.05mm, Silkscreens optimised, OSHW logo added.
2020-04-25 ATTiny412 Changed to ATTinyX12
    Revision2
2020-04-25 ATTiny1614 Changed to ATTinyX14
    Revision 2
2020-04-25 ATTiny1616 Changed to ATTinyX16
    Revision 2
2020-04-25 ATTiny3217 Changed to ATTinyX17
    Revision 2
2020-04-25 DS1307 Update
    Bypass Caps Added to Crystal
2020-04-25 ATTiny X12, X14 Silkscreen Revision
2020-04-25 ATTinyX14 Back Jpeg Update
2020-04-26 ATTiny85 Revision 2
    USB-C, SPX3819, QFN Package and Board Size Revision
2020-05-02 TSSOP
2020-05-02 SOIC
2020-05-02 MSSOP
2020-05-02 fix MSOP
2020-05-05 MAX3010X - Initial Commit
    SpO2 + Heart Rate Sensor
2020-05-08 ESP8266 Development Board - Initial Commit
    WiFi, MicroSD, USB-C Connector, SirBlue Connector with 5V Level Shift.
2020-05-10 Multiple Parts
2020-05-10 Fix LGA
2020-05-10 Crystal Resonator
2020-05-10 Mini USB
2020-05-11 CR1220 + RESISTOR ARRAY 4X0603
2020-05-12 Micro USB
2020-05-12 ESP8266 V1.3
    LED Deletes Added
2020-05-12 SIM28ML Revision2
    Active Antenna components removed, Battery connector changed
2020-05-12 SIM68ML Revision 2
    Active Antenna components removed, Battery connector changed
2020-05-12 SIM39EA Revision 2
    Battery connector changed and silkscreens rearranged
2020-05-13 SIM39EA Revision 2
    Battery Connected
2020-05-16 MINIMELF
2020-05-16 MICRO SD
2020-05-16 TYPE C USB
2020-05-23 ESP-WROOM32 Initial Commit
    ESP32 Dev Board
